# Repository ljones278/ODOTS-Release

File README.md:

# ODOTS Release Repository

This repository is intended to contain the latest basic ODOTS designs documentation and software, as well as be used as the source for the ODOTS homepage.

At the moment ODOTS is not covered by any license, this will change.

## ODOTS Release

At the moment development is continuing on a proof of concept design (that could be used if needed) which will be finished by the end of September 2019. Until this release all designs and software in the repository are primarily placeholders. Continuing development of the ODOTS is being recorded [here](https://justonemoreresistor.blogspot.com/search/label/ODOTS).

### Contributing

The ODOTS is still very early in its development, however if you have ideas for things you would like to add, questions about the design or require support in using the ODOTS, please contact me (l.jones278)

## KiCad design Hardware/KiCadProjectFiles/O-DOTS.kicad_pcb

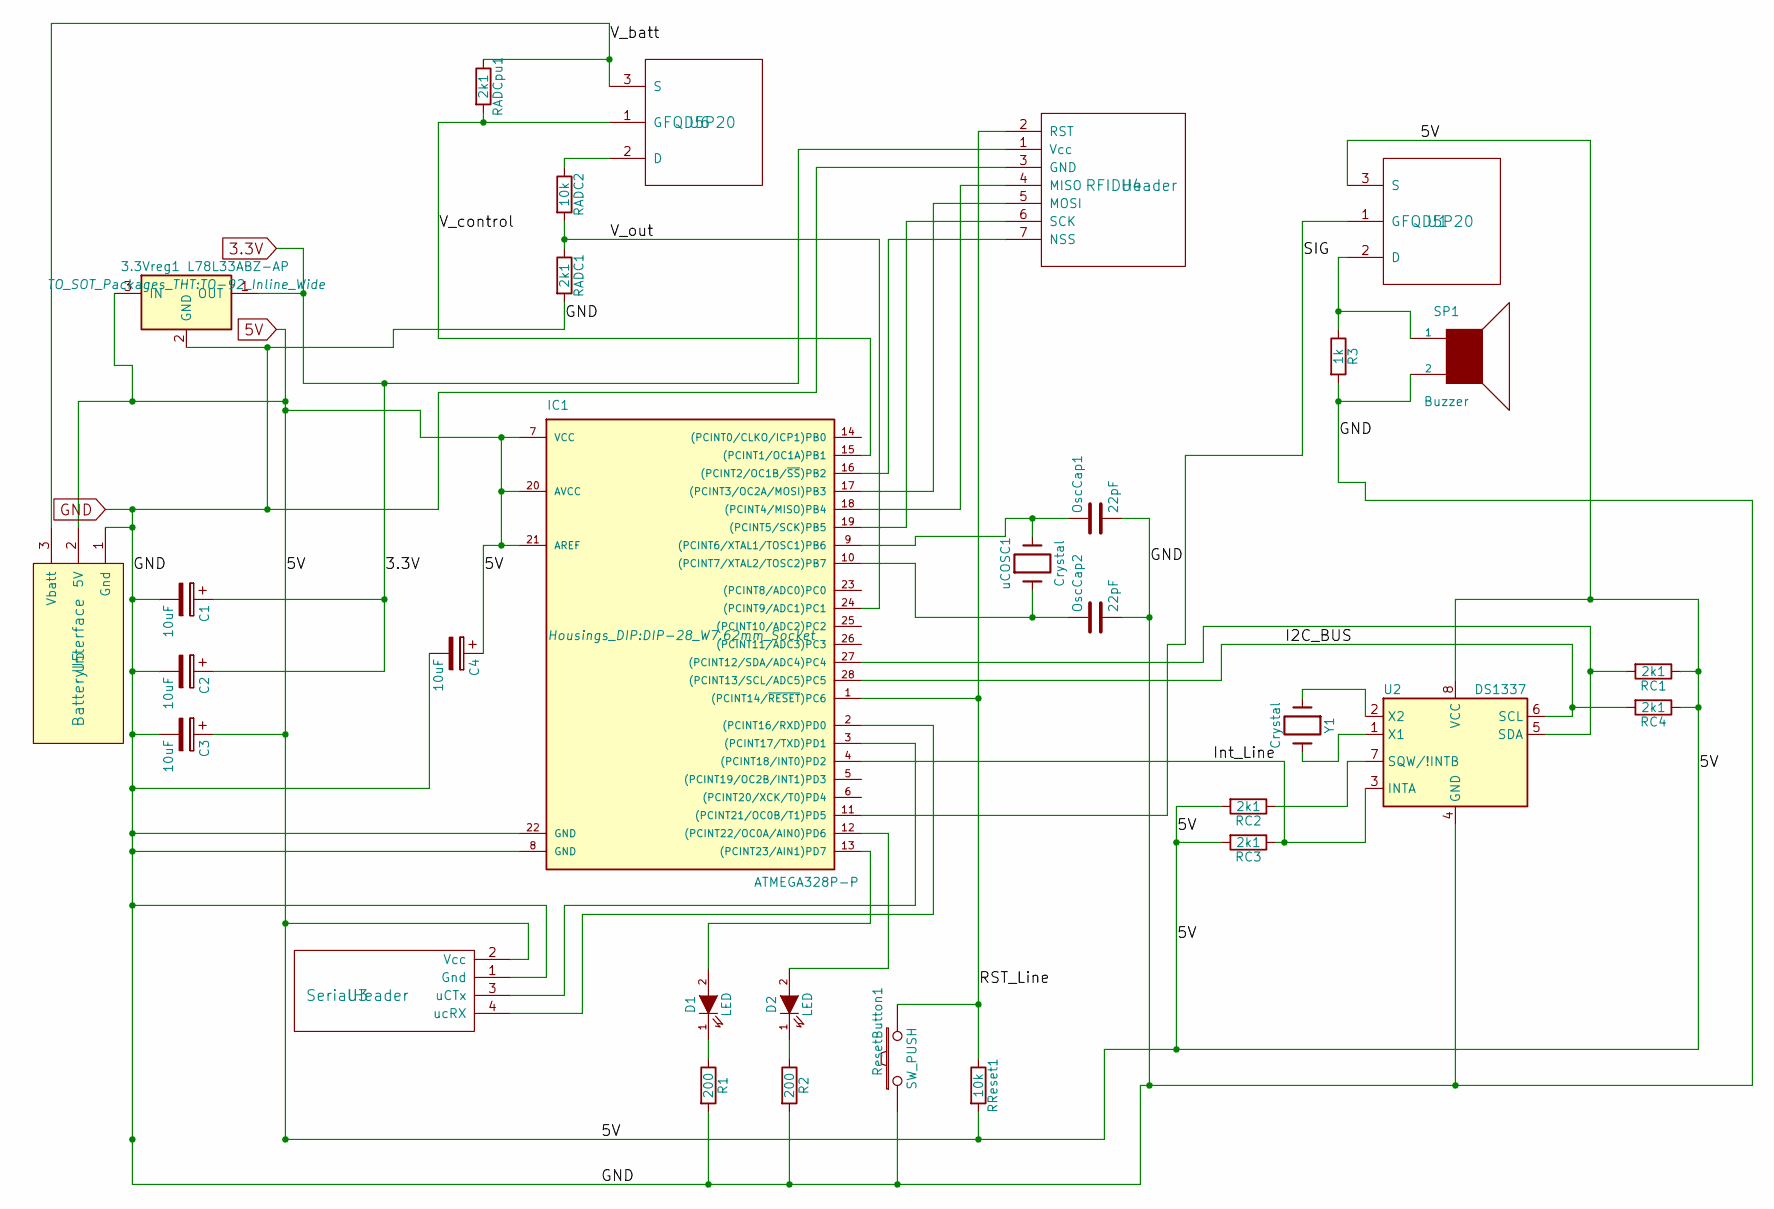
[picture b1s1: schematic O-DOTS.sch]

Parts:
3.3Vreg1: L78L33ABZ-AP; TO-92_Inline_Wide
C1, C2, C3, C4: 10uF; CP_Radial_D5.0mm_P2.50mm
D1, D2: LED; LED_D5.0mm
IC1: ATMEGA328P-P; DIP-28_W7.62mm_Socket
OscCap1, OscCap2: 22pF; C_Disc_D3.0mm_W1.6mm_P2.50mm
R1, R2: 200; R_Axial_DIN0204_L3.6mm_D1.6mm_P7.62mm_Horizontal
R3: 1k; R_Axial_DIN0204_L3.6mm_D1.6mm_P7.62mm_Horizontal
RADC1: 2k1; R_Axial_DIN0204_L3.6mm_D1.6mm_P7.62mm_Horizontal
RADC2: 10k; R_Axial_DIN0204_L3.6mm_D1.6mm_P7.62mm_Horizontal
RADCpu1: 2k1; R_Axial_DIN0204_L3.6mm_D1.6mm_P7.62mm_Horizontal
RC1, RC2, RC3, RC4: 2k1; R_Axial_DIN0204_L3.6mm_D1.6mm_P7.62mm_Horizontal
RReset1: 10k; R_Axial_DIN0204_L3.6mm_D1.6mm_P7.62mm_Horizontal
ResetButton1: SW_PUSH; SW_PUSH_6mm_h4.3mm
SP1: Buzzer; BUZZER
U1, U6: FQD5P20; TO-251_IPAK_Vertical
U2: DS1337; DIP-8_W7.62mm_Socket
U3: SerialHeader; Pin_Header_Straight_1x04_Pitch2.54mm
U4: RFIDHeader; Pin_Header_Straight_1x07_Pitch2.54mm
U5: BatteryInterface; Pin_Header_Straight_1x03_Pitch2.54mm
Y1: Crystal; Crystal_Round_d3.0mm_Vertical
uCOSC1: Crystal; Resonator-2pin_w10.0mm_h5.0mm

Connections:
3.3V: 3.3Vreg1.1 (OUT), C1.1, C2.1, U4.1 (Vcc)
5V: 3.3Vreg1.3 (IN), C3.1, C4.1, IC1.7 (VCC), IC1.20 (AVCC), IC1.21 (AREF), RC1.1, RC2.2, RC3.2, RC4.1, RReset1.2, U1.3 (S), U2.8 (VCC), U3.2 (Vcc), U5.2 (5V)
GND: 3.3Vreg1.2 (GND), C1.2, C2.2, C3.2, C4.2, IC1.8 (GND), IC1.22 (GND), OscCap1.2, OscCap2.2, R1.2, R2.2, R3.2, RADC1.2, ResetButton1.1, SP1.2, U2.4 (GND), U3.1 (Gnd), U4.3 (GND), U5.1 (Gnd)
unnamed: D1.1 (K), R1.1
unnamed: D1.2 (A), IC1.13 ((PCINT23/AIN1)PD7)
unnamed: D2.1 (K), R2.1
unnamed: D2.2 (A), IC1.12 ((PCINT22/OC0A/AIN0)PD6)
unnamed: IC1.1 ((PCINT14/~RESET~)PC6), RReset1.1, ResetButton1.2, U4.2 (RST)
unnamed: IC1.2 ((PCINT16/RXD)PD0), U3.4 (ucRX)
unnamed: IC1.3 ((PCINT17/TXD)PD1), U3.3 (uCTx)
unnamed: IC1.4 ((PCINT18/INT0)PD2), RC3.1, U2.3 (INTA)
unnamed: IC1.9 ((PCINT6/XTAL1/TOSC1)PB6), OscCap1.1, uCOSC1.2
unnamed: IC1.10 ((PCINT7/XTAL2/TOSC2)PB7), OscCap2.1, uCOSC1.1
unnamed: IC1.11 ((PCINT21/OC0B/T1)PD5), U1.1 (G)
unnamed: IC1.15 ((PCINT1/OC1A)PB1), RADCpu1.2, U6.1 (G)
unnamed: IC1.16 ((PCINT2/OC1B/~SS~)PB2), U4.7 (NSS)
unnamed: IC1.17 ((PCINT3/OC2A/MOSI)PB3), U4.5 (MOSI)
unnamed: IC1.18 ((PCINT4/MISO)PB4), U4.4 (MISO)
unnamed: IC1.19 ((PCINT5/SCK)PB5), U4.6 (SCK)
unnamed: IC1.24 ((PCINT9/ADC1)PC1), RADC1.1, RADC2.2
unnamed: IC1.27 ((PCINT12/SDA/ADC4)PC4), RC1.2, U2.5 (SDA)
unnamed: IC1.28 ((PCINT13/SCL/ADC5)PC5), RC4.2, U2.6 (SCL)
unnamed: R3.1, SP1.1, U1.2 (D)
unnamed: RADC2.1, U6.2 (D)
unnamed: RADCpu1.1, U5.3 (Vbatt), U6.3 (S)
unnamed: RC2.1, U2.7 (SQW/!INTB)
unnamed: U2.1 (X1), Y1.2
unnamed: U2.2 (X2), Y1.1

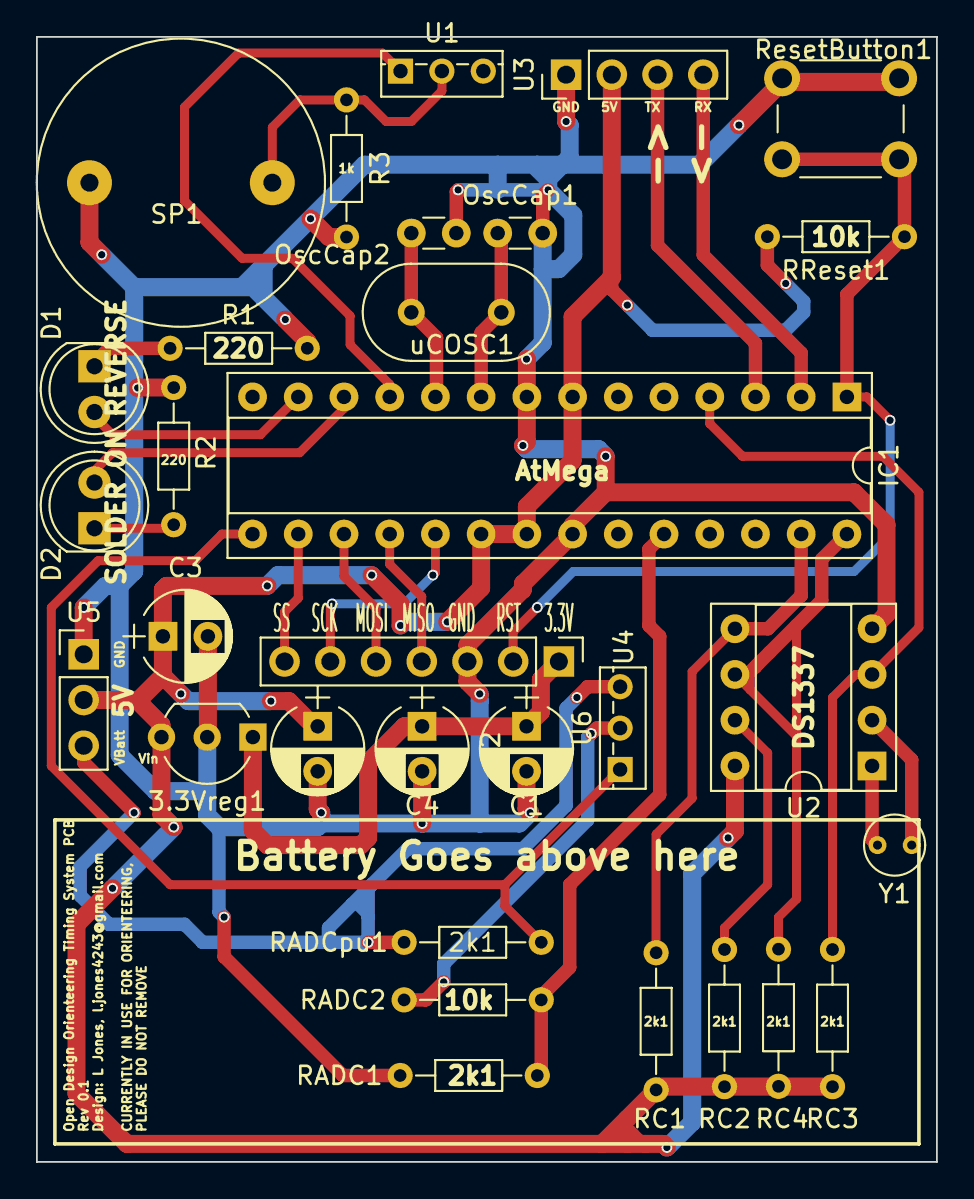
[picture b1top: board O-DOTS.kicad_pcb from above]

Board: 2 copper layers, 50.0 x 62.5 mm, 31 parts (0 on the bottom side), 28 nets.

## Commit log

2019-09-10 Set theme jekyll-theme-cayman
2019-09-10 Initial commit with all relevant files
2019-09-10 Rewrote main page
2019-09-10 Stupid
2019-09-10 Moar stupid
2019-09-10 Even more
2019-09-10 dev update 1 - change of header
2019-09-10 Update Style
2019-09-10 further updates
2019-09-10 more trouble shooting
2019-09-10 whoops
2019-09-10 fixed
2019-09-10 fixed colour gradient
2019-09-10 interesting
2019-09-10 try again
2019-09-10 Update to repository read-me
2019-09-10 Readme update, more styling
2019-09-10 More styling, adding the logo to the webpage
2019-09-10 blobbing
2019-09-10 more html fun
2019-09-10 read the help page
2019-09-10 more testing
2019-09-10 fixed the title colour
2019-09-10 tried rerouting logo path
2019-09-10 adjusted header width
2019-09-10 title update
2019-09-10 re-routed specification and user manual link!
2019-09-18 Updates, included firmware!
2019-09-18 updated pcb stuff
2019-09-23 Interface pyinstaller magic
2019-09-23 update to website
2019-09-23 markdown syntax error!
2019-09-24 Added JRE check
2019-09-24 One File Interface
2019-09-27 update to progress current work section of web page
2019-10-01 User guide update for finalised proof of concept design
2019-10-06 Update of documentation
2019-10-09 Update to readme
